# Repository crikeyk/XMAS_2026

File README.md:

# XMAS_2026

Christmas 2026 persistence-of-vision display.

## Contents

- `PCB/` — KiCad project `XMAS_2026` (schematic and board)
- `Firmware/` — wand firmware. The current program is the RP2350 C firmware in `Firmware/rp2350/`

## Origin

Copied from [PoV_display_PoC](https://github.com/crikeyk/PoV_display_PoC) at `458e425`, then the KiCad project was renamed to `XMAS_2026`.

## Libraries

The handmade parts are in the private [kicad-library](https://github.com/crikeyk/kicad-library) repo: the `TLV74311PDBVR` symbol and the `BC-8200 AAA Battery clip` footprint. Clone it next to this project (`Documents/Code/kicad-library`) so `PCB/sym-lib-table` and `PCB/fp-lib-table` resolve `${KIPRJMOD}/../../kicad-library`.

The other symbols and footprints are the [JLCPCB KiCad library](https://github.com/CDFER/JLCPCB-Kicad-Library), installed through KiCad's Plugin and Content Manager. Use the 2026.08.08 package. The newer 2026.09.21 package is missing the generated parts.

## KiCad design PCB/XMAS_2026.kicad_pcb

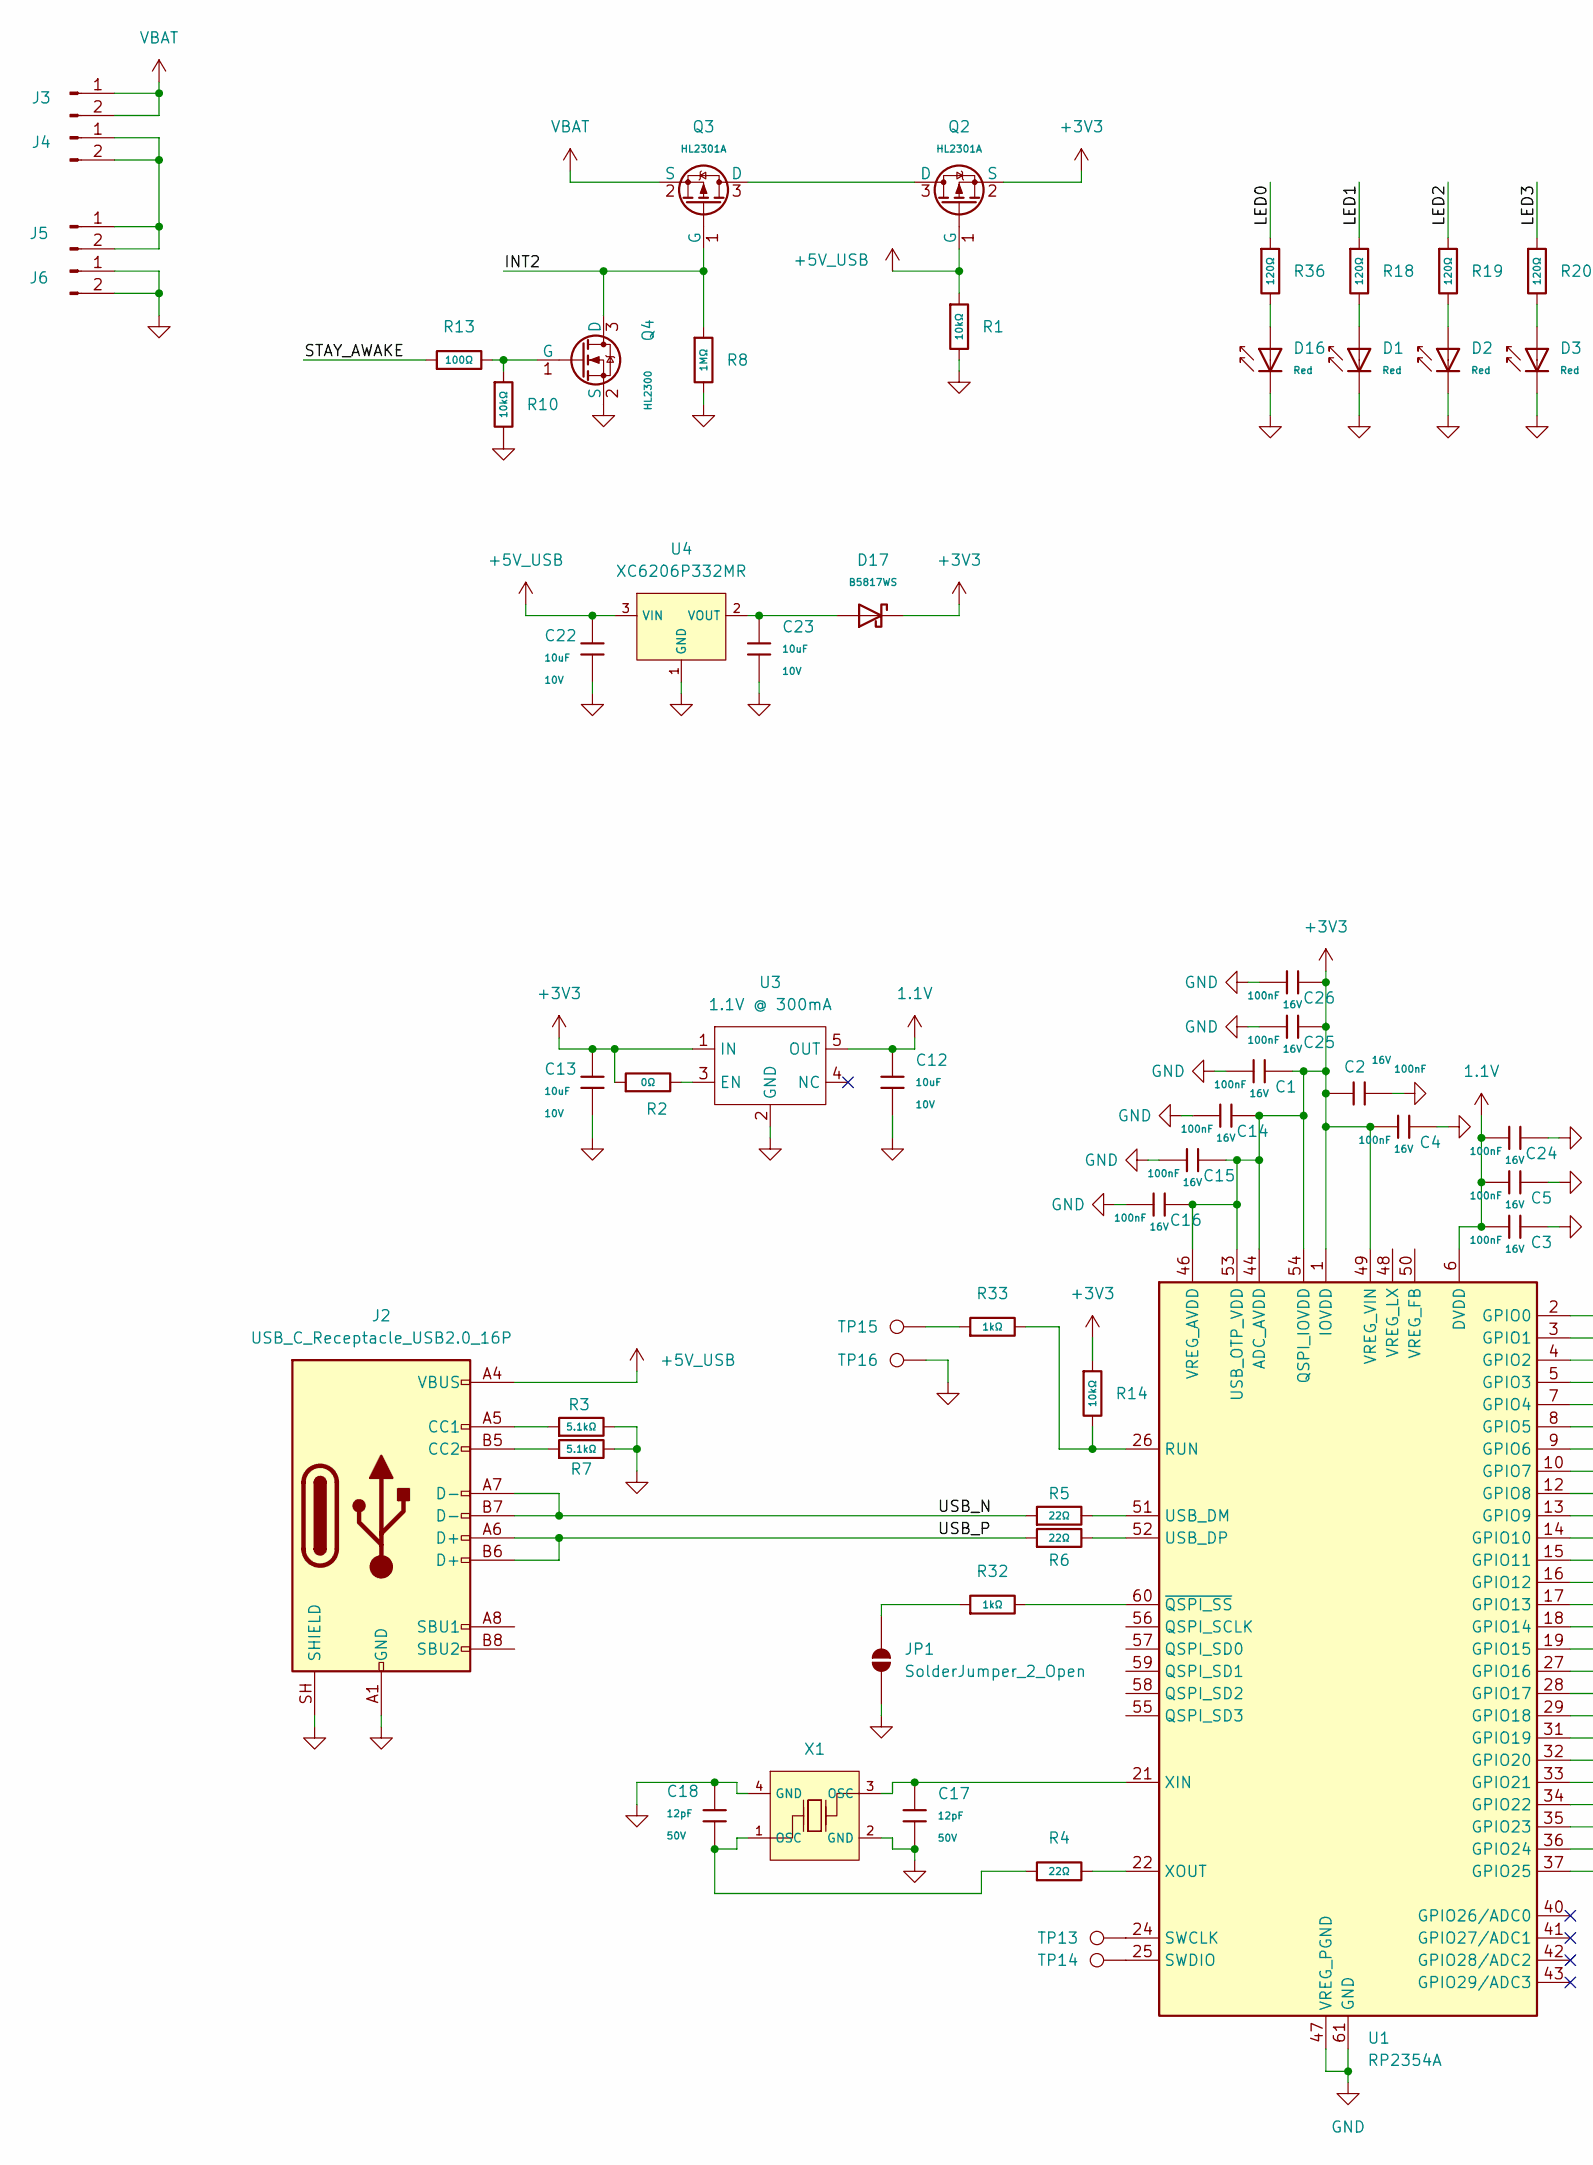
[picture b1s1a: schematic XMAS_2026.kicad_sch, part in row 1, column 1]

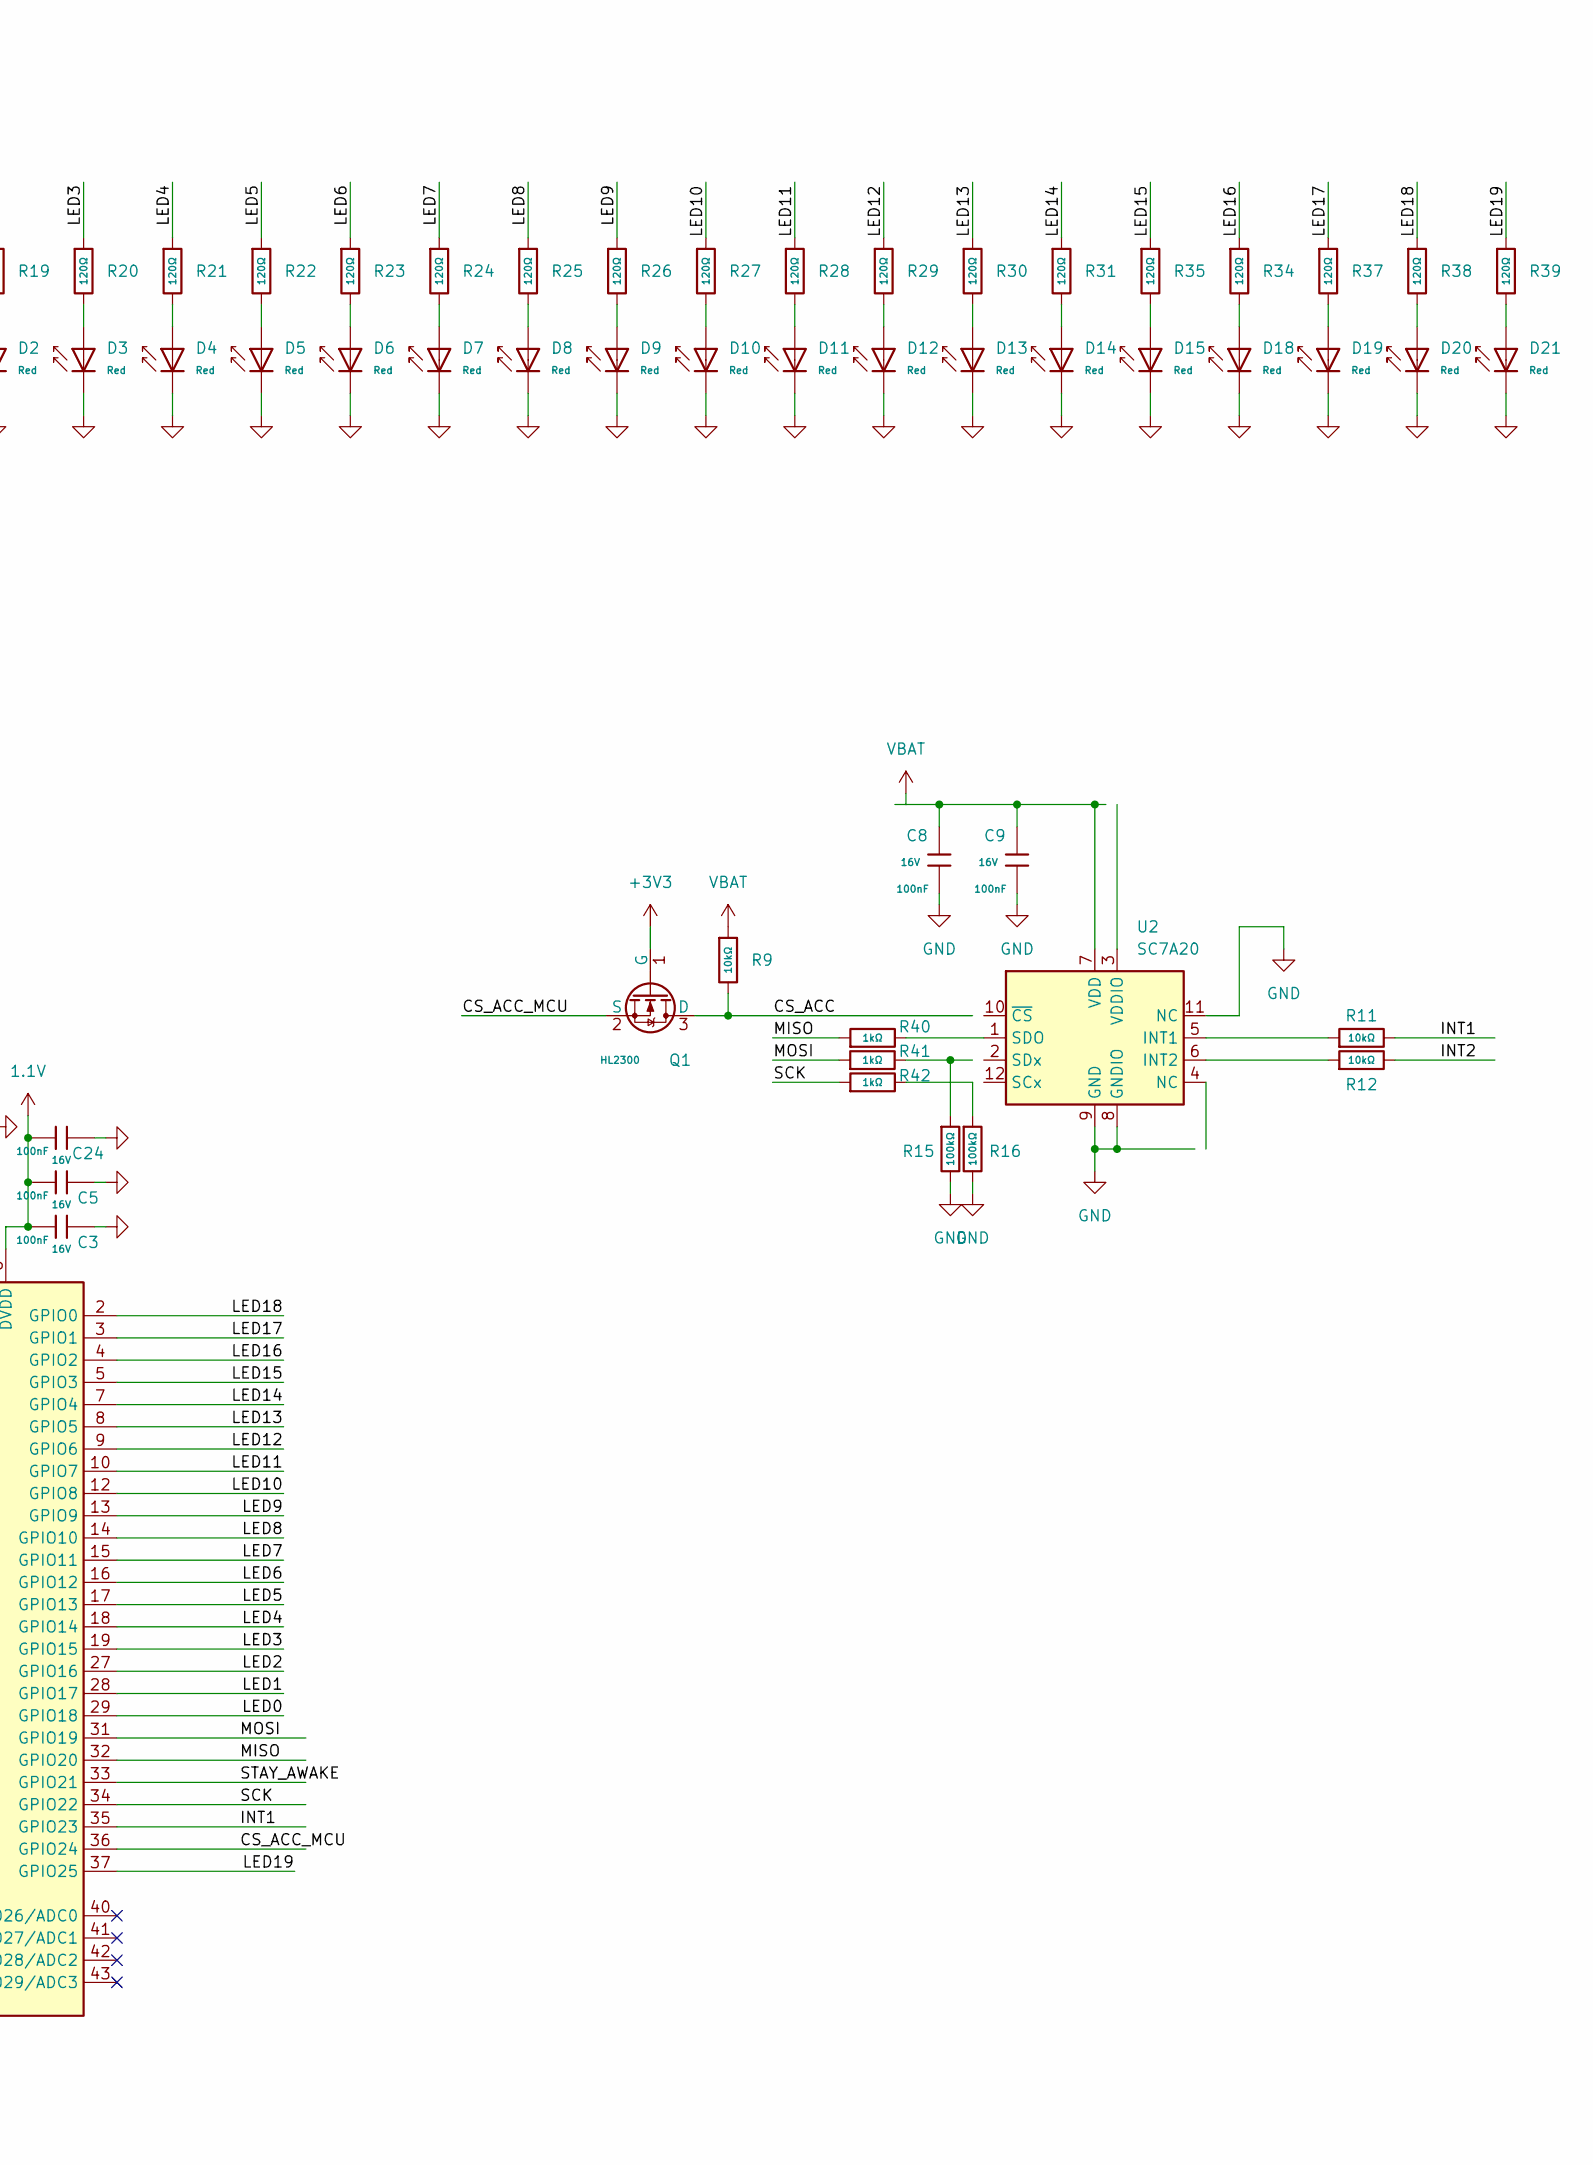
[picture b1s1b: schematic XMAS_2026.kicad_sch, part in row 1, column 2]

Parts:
C1, C2, C3, C4, C5, C8, C9, C14, C15, C16, C24, C25, C26: 100nF; C_0402; Voltage Rated 16V; Tolerance ±10%; Part CL05B104KO5NNNC; LCSC C1525
C12, C13, C22, C23: 10uF; C_0603; Voltage Rated 10V; Tolerance ±10%; Part CL10A106KP8NNNC; LCSC C19702
C17, C18: 12pF; C_0402; Voltage Rated 50V; Tolerance ±5%; Part 0402CG120J500NT; LCSC C1547
D1, D2, D3, D4, D5, D6, D7, D8, D9, D10, D11, D12, D13, D14, D15, D16, D18, D19, D20, D21: Red; D_0603; Part KT-0603R; LCSC C2286
D17: B5817WS; D_SOD-323; Forward Voltage (Vf@If) 450mV@1.0A; Reverse Voltage (Vr) 20V; Part B5817WS; LCSC C7420329
J2: USB_C_Receptacle_USB2.0_16P; USB_C_Receptacle_HRO_TYPE-C-31-M-12; LCSC C165948
J3, J4, J5, J6: Conn_01x02_Pin; BC-8200 AAA Battery clip; LCSC C2979181
JP1: SolderJumper_2_Open; SolderJumper-2_P1.3mm_Open_TrianglePad1.0x1.5mm
Q1, Q4: HL2300; Q_SOT-23; Part HL2300; LCSC C7420343
Q2, Q3: HL2301A; Q_SOT-23; Part HL2301A; LCSC C7420344
R1, R9, R10, R11, R12, R14: 10kΩ; R_0402; Overload Voltage (Max) 50V; Tolerance ±1%; Part 0402WGF1002TCE; LCSC C25744
R2: 0Ω; R_0402; Overload Voltage (Max) 50V; Tolerance ±1%; Part 0402WGF0000TCE; LCSC C17168
R3, R7: 5.1kΩ; R_0402; Overload Voltage (Max) 50V; Tolerance ±1%; Part 0402WGF5101TCE; LCSC C25905
R4, R5, R6: 22Ω; R_0402; Overload Voltage (Max) 50V; Tolerance ±1%; Part 0402WGF220JTCE; LCSC C25092
R8: 1MΩ; R_0402; Overload Voltage (Max) 50V; Tolerance ±1%; Part 0402WGF1004TCE; LCSC C26083
R13: 100Ω; R_0402; Overload Voltage (Max) 50V; Tolerance ±1%; Part 0402WGF1000TCE; LCSC C25076
R15, R16: 100kΩ; R_0402; Overload Voltage (Max) 50V; Tolerance ±1%; Part 0402WGF1003TCE; LCSC C25741
R18, R19, R20, R21, R22, R23, R24, R25, R26, R27, R28, R29, R30, R31, R34, R35, R36, R37, R38, R39: 120Ω; R_0603; Overload Voltage (Max) 75V; Tolerance ±1%; Part 0603WAF1200T5E; LCSC C22787
R32, R33, R40, R41, R42: 1kΩ; R_0402; Overload Voltage (Max) 50V; Tolerance ±1%; Part 0402WGF1001TCE; LCSC C11702
TP13, TP14, TP15, TP16: TestPoint; TestPoint_Pad_D1.0mm
U1: RP2354A; QFN-60-1EP_7x7mm_P0.4mm_EP3.4x3.4mm; LCSC C41378174
U2: SC7A20; LGA-12_2x2mm_P0.5mm; LCSC C19274408
U3: 1.1V @ 300mA; SOT-23-5; LCSC C485147
U4: XC6206P332MR; SOT-23-3_L2.9-W1.6-P1.90-LS2.8-BR; Output Voltage 3.3V; Dropout Voltage 680mV@(100mA); Part XC6206P332MR-G; LCSC C5446
X1: X322512MSB4SI; CRYSTAL-SMD_4P-L3.2-W2.5-BL; Frequency Tolerance ±10ppm; Part X322512MSB4SI; LCSC C9002

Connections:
1.1V: C3.2, C5.2, C12.1, C24.2, U1.6 (DVDD), U1.23 (DVDD), U1.39 (DVDD), U3.5 (OUT)
+3V3: C1.1, C2.1, C4.2, C13.1, C14.1, C15.1, C16.1, C25.1, C26.1, D17.1, Q1.1 (G), Q2.2 (S), R2.1, R14.1, U1.1 (IOVDD), U1.11 (IOVDD), U1.20 (IOVDD), U1.30 (IOVDD), U1.38 (IOVDD), U1.44 (ADC_AVDD), U1.45 (IOVDD), U1.46 (VREG_AVDD), U1.49 (VREG_VIN), U1.53 (USB_OTP_VDD), U1.54 (QSPI_IOVDD), U3.1 (IN)
+5V_USB: C22.1, J2.A4 (VBUS), J2.A9 (VBUS), J2.B4 (VBUS), J2.B9 (VBUS), Q2.1 (G), R1.1, U4.3 (VIN)
/CS_ACC: Q1.3 (D), R9.2
/CS_ACC_MCU: Q1.2 (S), U1.36 (GPIO24)
/INT1: R11.2, U1.35 (GPIO23)
/INT2: Q3.1 (G), Q4.3 (D), R8.1, R12.2
/LED0: R36.1, U1.29 (GPIO18)
/LED1: R18.1, U1.28 (GPIO17)
/LED2: R19.1, U1.27 (GPIO16)
/LED3: R20.1, U1.19 (GPIO15)
/LED4: R21.1, U1.18 (GPIO14)
/LED5: R22.1, U1.17 (GPIO13)
/LED6: R23.1, U1.16 (GPIO12)
/LED7: R24.1, U1.15 (GPIO11)
/LED8: R25.1, U1.14 (GPIO10)
/LED9: R26.1, U1.13 (GPIO9)
/LED10: R27.1, U1.12 (GPIO8)
/LED11: R28.1, U1.10 (GPIO7)
/LED12: R29.1, U1.9 (GPIO6)
/LED13: R30.1, U1.8 (GPIO5)
/LED14: R31.1, U1.7 (GPIO4)
/LED15: R35.1, U1.5 (GPIO3)
/LED16: R34.1, U1.4 (GPIO2)
/LED17: R37.1, U1.3 (GPIO1)
/LED18: R38.1, U1.2 (GPIO0)
/LED19: R39.1, U1.37 (GPIO25)
/MISO: R40.1, U1.32 (GPIO20)
/MOSI: R41.1, U1.31 (GPIO19)
/SCK: R42.1, U1.34 (GPIO22)
/STAY_AWAKE: R13.1, U1.33 (GPIO21)
/USB_N: J2.A7 (D-), J2.B7 (D-), R5.1
/USB_P: J2.A6 (D+), J2.B6 (D+), R6.1
GND: C1.2, C2.2, C3.1, C4.1, C5.1, C8.2, C9.2, C12.2, C13.2, C14.2, C15.2, C16.2, C17.2, C18.2, C22.2, C23.2, C24.1, C25.2, C26.2, D1.1, D2.1, D3.1, D4.1, D5.1, D6.1, D7.1, D8.1, D9.1, D10.1, D11.1, D12.1, D13.1, D14.1, D15.1, D16.1, D18.1, D19.1, D20.1, D21.1, J2.A1 (GND), J2.A12 (GND), J2.B1 (GND), J2.B12 (GND), J2.SH (SHIELD), J6.1, J6.2, JP1.1 (A), Q4.2 (S), R1.2, R3.2, R7.2, R8.2, R10.2, R15.2, R16.2, TP16.1 (1_1), U1.47 (VREG_PGND), U1.61 (GND), U2.8 (GNDIO), U2.9 (GND), U2.11 (NC), U3.2 (GND), U4.1 (GND), X1.2 (GND), X1.4 (GND)
unnamed: C18.1, R4.1, X1.1 (OSC)
unnamed: D1.2, R18.2
unnamed: D2.2, R19.2
unnamed: D3.2, R20.2
unnamed: D4.2, R21.2
unnamed: D5.2, R22.2
unnamed: D6.2, R23.2
unnamed: D7.2, R24.2
unnamed: D8.2, R25.2
unnamed: D9.2, R26.2
unnamed: D10.2, R27.2
unnamed: D11.2, R28.2
unnamed: D12.2, R29.2
unnamed: D13.2, R30.2
unnamed: D14.2, R31.2
unnamed: D15.2, R35.2
unnamed: D16.2, R36.2
unnamed: D18.2, R34.2
unnamed: D19.2, R37.2
unnamed: D20.2, R38.2
unnamed: D21.2, R39.2
unnamed: J2.A5 (CC1), R3.1
unnamed: J2.B5 (CC2), R7.1
unnamed: J4.1, J4.2, J5.1, J5.2
unnamed: JP1.2 (B), R32.1
unnamed: Q2.3 (D), Q3.3 (D)
unnamed: Q4.1 (G), R10.1, R13.2
unnamed: R15.1, R41.2
unnamed: R16.1, R42.2
unnamed: R33.1, TP15.1 (1_1)
unnamed: R14.2, R33.2, U1.26 (RUN)
unnamed: TP13.1 (1_1), U1.24 (SWCLK)
unnamed: TP14.1 (1_1), U1.25 (SWDIO)
unnamed: R5.2, U1.51 (USB_DM)
unnamed: R6.2, U1.52 (USB_DP)
unnamed: C17.1, U1.21 (XIN), X1.3 (OSC)
unnamed: R4.2, U1.22 (XOUT)
unnamed: R32.2, U1.60 (~QSPI_SS)
unnamed: R11.1, U2.5 (INT1)
unnamed: R12.1, U2.6 (INT2)
unnamed: R40.2, U2.1 (SDO)
unnamed: C8.1, C9.1, U2.7 (VDD)
unnamed: R2.2, U3.3 (EN)
unnamed: C23.1, D17.2, U4.2 (VOUT)
VBAT: J3.1, J3.2, Q3.2 (S), R9.1

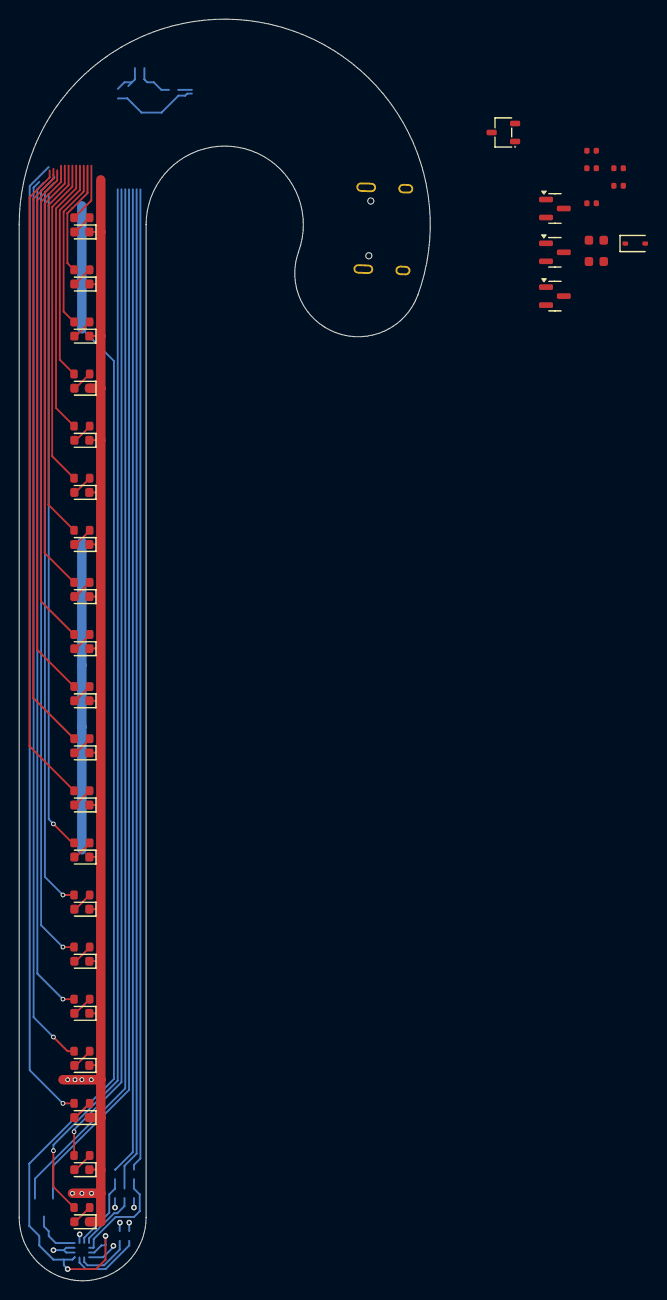
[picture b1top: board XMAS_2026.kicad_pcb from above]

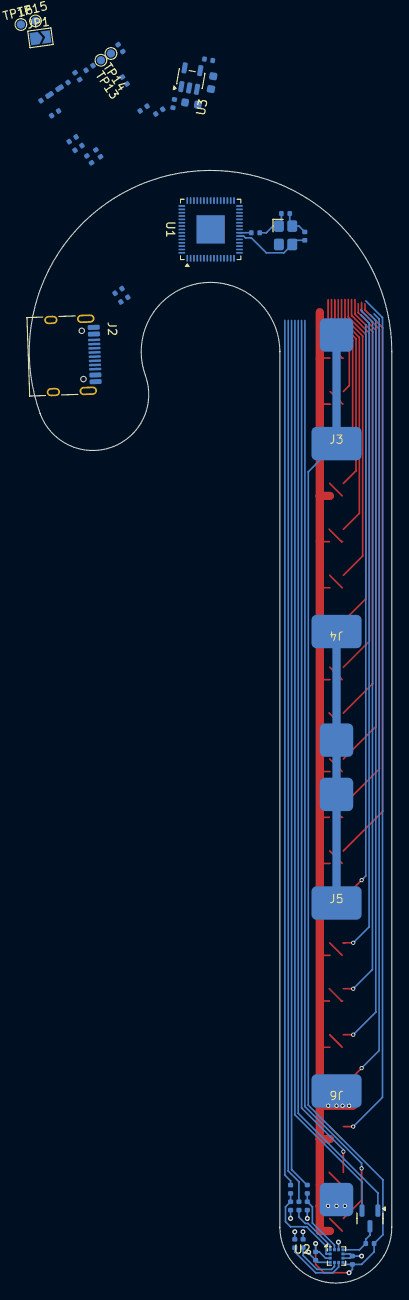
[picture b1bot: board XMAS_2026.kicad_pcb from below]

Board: 4 copper layers, 43.4 x 133.2 mm, 100 parts (48 on the bottom side), 79 nets.

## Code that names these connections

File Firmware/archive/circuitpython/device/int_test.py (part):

# int_test.py - SC7A20 INT1 / INT2 hardware check: which level is "active", and are the pins driven or released?
#
# HOW TO RUN (pick one):
#   1. Put   INT_TEST = yes   in settings.txt. code.py runs this test at boot, then carries on as normal.
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    buf6 = bytearray(6)
    cmd6 = bytes([0x28 | 0xC0])
    cath = leds._cath
    names = ("INT1 (GPIO23)", "INT2 (GPIO21)")

    pins = []
    try:
        for pn in (microcontroller.pin.GPIO23, microcontroller.pin.GPIO21):
            d = digitalio.DigitalInOut(pn)
            d.switch_to_input(pull=None)
            pins.append(d)
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        wr(0x24, 0x0A)                      # CTRL_REG5: LIR_INT1 + LIR_INT2 = latch both until their SOURCE register is read
        wr(0x32, THS); wr(0x33, 1); wr(0x30, 0x2A)    # generator 1: OR of X/Y/Z high, 1 sample
        wr(0x36, THS); wr(0x37, 1); wr(0x34, 0x2A)    # generator 2: same
        wr(0x22, 0x40)                      # CTRL_REG3: I1_AOI1 -> INT1 pin
        # CTRL_REG6: I2_INT1 (0x40) + I2_INT2 (0x20) -> INT2 pin carries both generators (the datasheet text for these two
        # bits is ambiguous, so enable both); bit 1 = H_LACTIVE
        wr(0x25, 0x60 | (0x02 if active_low else 0x00))

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                print("INT>   t=%.2fs: motion seen in x/y/z (%d/%d/%d counts)" % (now - t0, cx - x0, cy - y0, cz - z0))
            if lv != base and t_pin is None:
                t_pin = now
                print("INT>   t=%.2fs: PIN CHANGE  INT1 %d->%d  INT2 %d->%d" % (now - t0, base[0], lv[0], base[1], lv[1]))
                why = "pin change"
                break
            if t_move is not None and now - t_move > 0.5:
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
